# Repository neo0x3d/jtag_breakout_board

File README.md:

# jtag_breakout_board

# This project has been moved to Gitlab: <https://gitlab.com/users/neo0x3d/projects>

JTAG/SWD breakout board

Accommodates following headers:
* 2x10 pin 100mil/2.54mm (shrouded)
* 2x10 pin 100mil/2.54mm (unshrouded)
* 2x10, 19pin 50 mil/1.27mm
* 2x5, 9 pin 50 mil/1.27mm

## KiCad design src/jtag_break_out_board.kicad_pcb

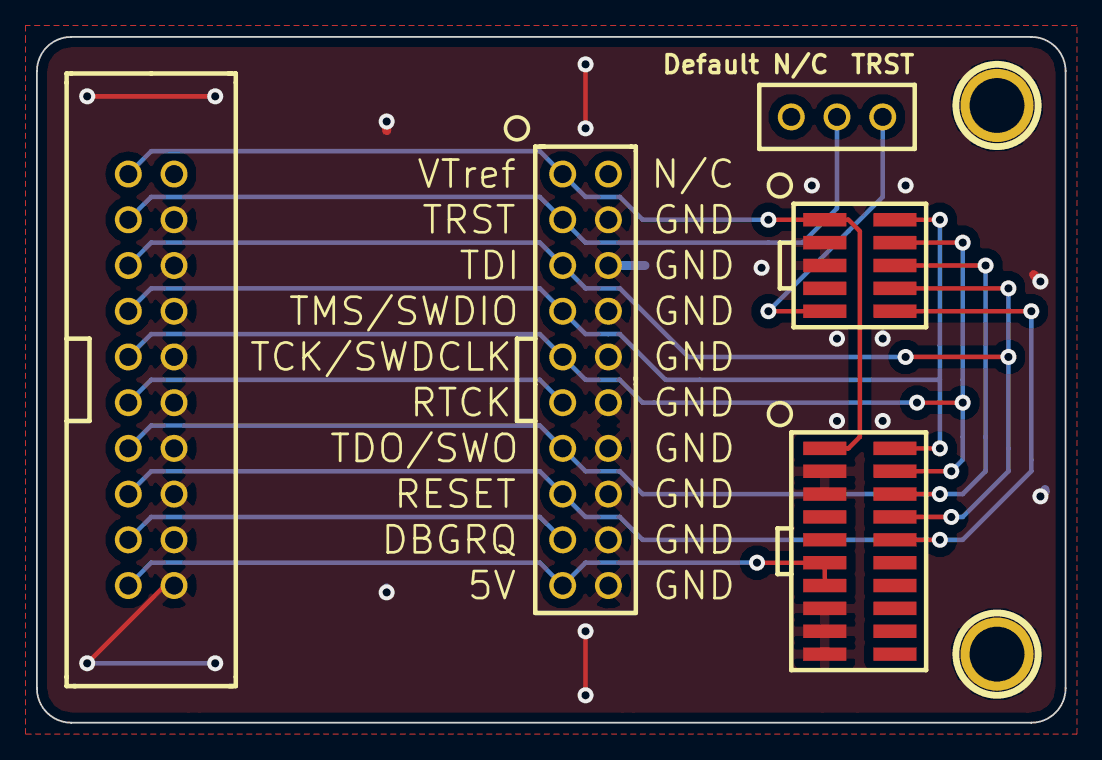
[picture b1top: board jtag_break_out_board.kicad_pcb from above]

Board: 2 copper layers, 57.2 x 38.1 mm, 7 parts (0 on the bottom side), 13 nets.

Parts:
1PIN, 1PIN#2: P***; 1pin
Jumper1: CONN_3; 3P_Jumper
U2: CONN_5X2; 2x5_9P_50mil_smd
U3: CONN_10X2; 2x10_JTAG_shrouded
U4: CONN_10X2; 2x10_19P_50mil_smd
U5: CONN_10X2; 2x10_JTAG_SWD_labeled

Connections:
5V-Supply: U3.19, U4.11, U4.13, U5.19
DBGRQ: U3.17, U5.17
GND: 1PIN.1, 1PIN#2.1, U2.3, U2.5, U3.4, U3.6, U3.8, U3.10, U3.12, U3.14, U3.16, U3.18, U3.20, U4.3, U4.5, U4.15, U4.17, U4.19, U5.4, U5.6, U5.8, U5.10, U5.12, U5.14, U5.16, U5.18, U5.20
KEY_Pin: U2.7, U4.7
unnamed: Jumper1.1, U2.9
RESET: U2.10, U3.15, U4.10, U5.15
RTCK: U3.11, U5.11
TCK/SWDCLK: U2.4, U3.9, U4.4, U5.9
TDI: U2.8, U3.5, U4.8, U5.5
TDO/SWO: U2.6, U3.13, U4.6, U5.13
TMS/SWDIO: U2.2, U3.7, U4.2, U5.7
TRST: Jumper1.2, U3.3, U5.3
VTref: U2.1, U3.1, U4.1, U5.1

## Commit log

2016-08-23 initial README.md change
2017-03-10 changed to gitlab
